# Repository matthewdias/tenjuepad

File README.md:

# tenjuepad
low pro wireless numpad

- choc switches
- designed with nice!nano in mind
- battery headers
- power switch
- art by [pokexe](https://twitter.com/pokexe_art)

## bill of materials

- [Power switch](https://www.mouser.com/ProductDetail/Alps-Alpine/SSAJ120100/?qs=35GPJvxY%252Bl5mRNwFoBrl2g%3D%3D) (optional)
- battery (optional)
- 22 diodes
- nice!nano or other pro micro compatible controller board
- 8 m2 screws
- 4 m2 6mm hex standoffs
- 2 midplates cut from the svg file 3mm thick

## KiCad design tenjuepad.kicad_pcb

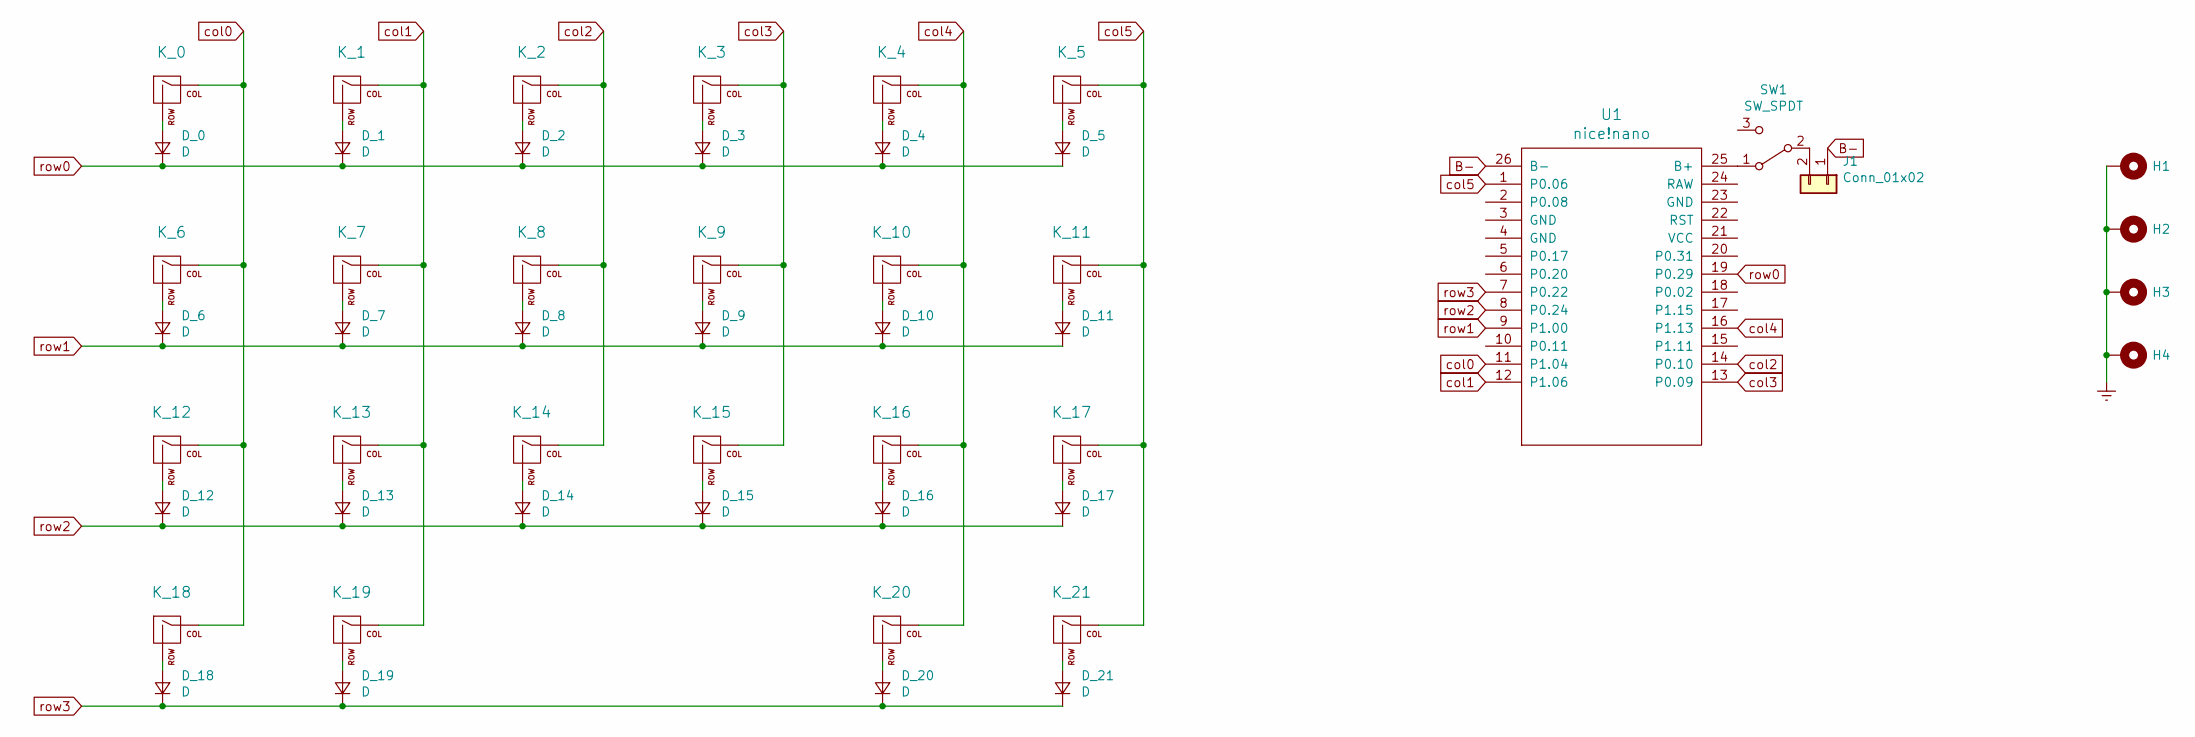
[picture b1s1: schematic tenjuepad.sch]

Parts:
D_0, D_1, D_2, D_3, D_4, D_5, D_6, D_7, D_8, D_9, D_10, D_11, D_12, D_13, D_14, D_15, D_16, D_17, D_18, D_19, D_20, D_21: D; Diode-Hybrid-Back
H1, H2, H3, H4: MountingHole_Pad; MountingHole_2.2mm_M2_Pad_Via
J1: Conn_01x02; PinHeader_1x02_P2.54mm_Vertical
K_0, K_1, K_2, K_3, K_4, K_5, K_6, K_7, K_8, K_9, K_10, K_11, K_12, K_13, K_14, K_15, K_16, K_17, K_18, K_19, K_20, K_21: KEYSW; KailhChoc-1U
SW1: SW_SPDT; SSAJ120100
U1: nice!nano; nicenano

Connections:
B-: J1.1, U1.26 (B-)
Earth: H1.1, H2.1, H3.1, H4.1
unnamed: D_0.2 (A), K_0.2 (ROW)
unnamed: D_1.2 (A), K_1.2 (ROW)
unnamed: D_2.2 (A), K_2.2 (ROW)
unnamed: D_3.2 (A), K_3.2 (ROW)
unnamed: D_4.2 (A), K_4.2 (ROW)
unnamed: D_5.2 (A), K_5.2 (ROW)
unnamed: D_6.2 (A), K_6.2 (ROW)
unnamed: D_7.2 (A), K_7.2 (ROW)
unnamed: D_8.2 (A), K_8.2 (ROW)
unnamed: D_9.2 (A), K_9.2 (ROW)
unnamed: D_10.2 (A), K_10.2 (ROW)
unnamed: D_11.2 (A), K_11.2 (ROW)
unnamed: D_12.2 (A), K_12.2 (ROW)
unnamed: D_13.2 (A), K_13.2 (ROW)
unnamed: D_14.2 (A), K_14.2 (ROW)
unnamed: D_15.2 (A), K_15.2 (ROW)
unnamed: D_16.2 (A), K_16.2 (ROW)
unnamed: D_17.2 (A), K_17.2 (ROW)
unnamed: D_18.2 (A), K_18.2 (ROW)
unnamed: D_19.2 (A), K_19.2 (ROW)
unnamed: D_20.2 (A), K_20.2 (ROW)
unnamed: D_21.2 (A), K_21.2 (ROW)
unnamed: J1.2, SW1.2 (B)
unnamed: SW1.1 (A), U1.25 (B+)
col0: K_0.1 (COL), K_6.1 (COL), K_12.1 (COL), K_18.1 (COL), U1.11 (P1.04)
col1: K_1.1 (COL), K_7.1 (COL), K_13.1 (COL), K_19.1 (COL), U1.12 (P1.06)
col2: K_2.1 (COL), K_8.1 (COL), K_14.1 (COL), U1.14 (P0.10)
col3: K_3.1 (COL), K_9.1 (COL), K_15.1 (COL), U1.13 (P0.09)
col4: K_4.1 (COL), K_10.1 (COL), K_16.1 (COL), K_20.1 (COL), U1.16 (P1.13)
col5: K_5.1 (COL), K_11.1 (COL), K_17.1 (COL), K_21.1 (COL), U1.1 (P0.06)
row0: D_0.1 (K), D_1.1 (K), D_2.1 (K), D_3.1 (K), D_4.1 (K), D_5.1 (K), U1.19 (P0.29)
row1: D_6.1 (K), D_7.1 (K), D_8.1 (K), D_9.1 (K), D_10.1 (K), D_11.1 (K), U1.9 (P1.00)
row2: D_12.1 (K), D_13.1 (K), D_14.1 (K), D_15.1 (K), D_16.1 (K), D_17.1 (K), U1.8 (P0.24)
row3: D_18.1 (K), D_19.1 (K), D_20.1 (K), D_21.1 (K), U1.7 (P0.22)

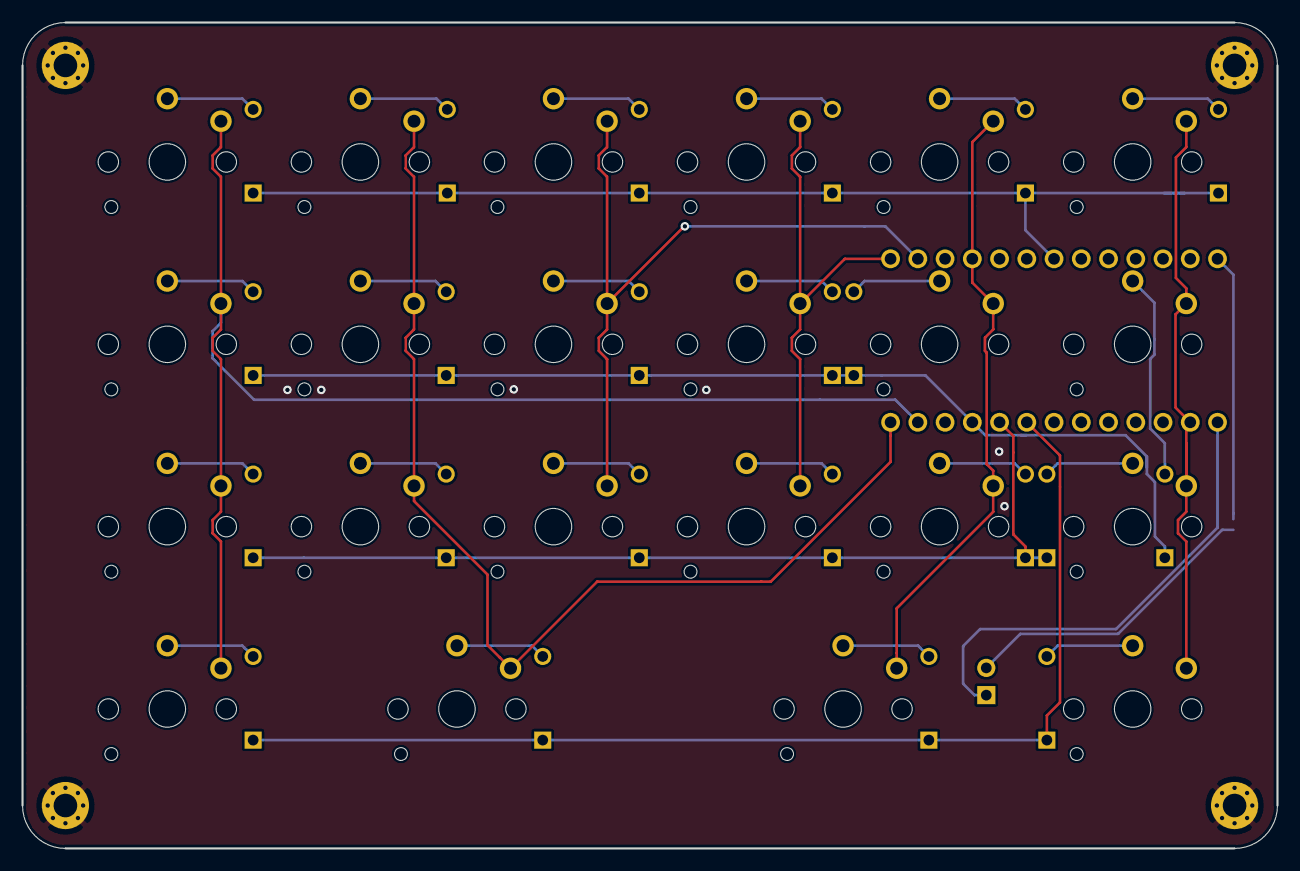
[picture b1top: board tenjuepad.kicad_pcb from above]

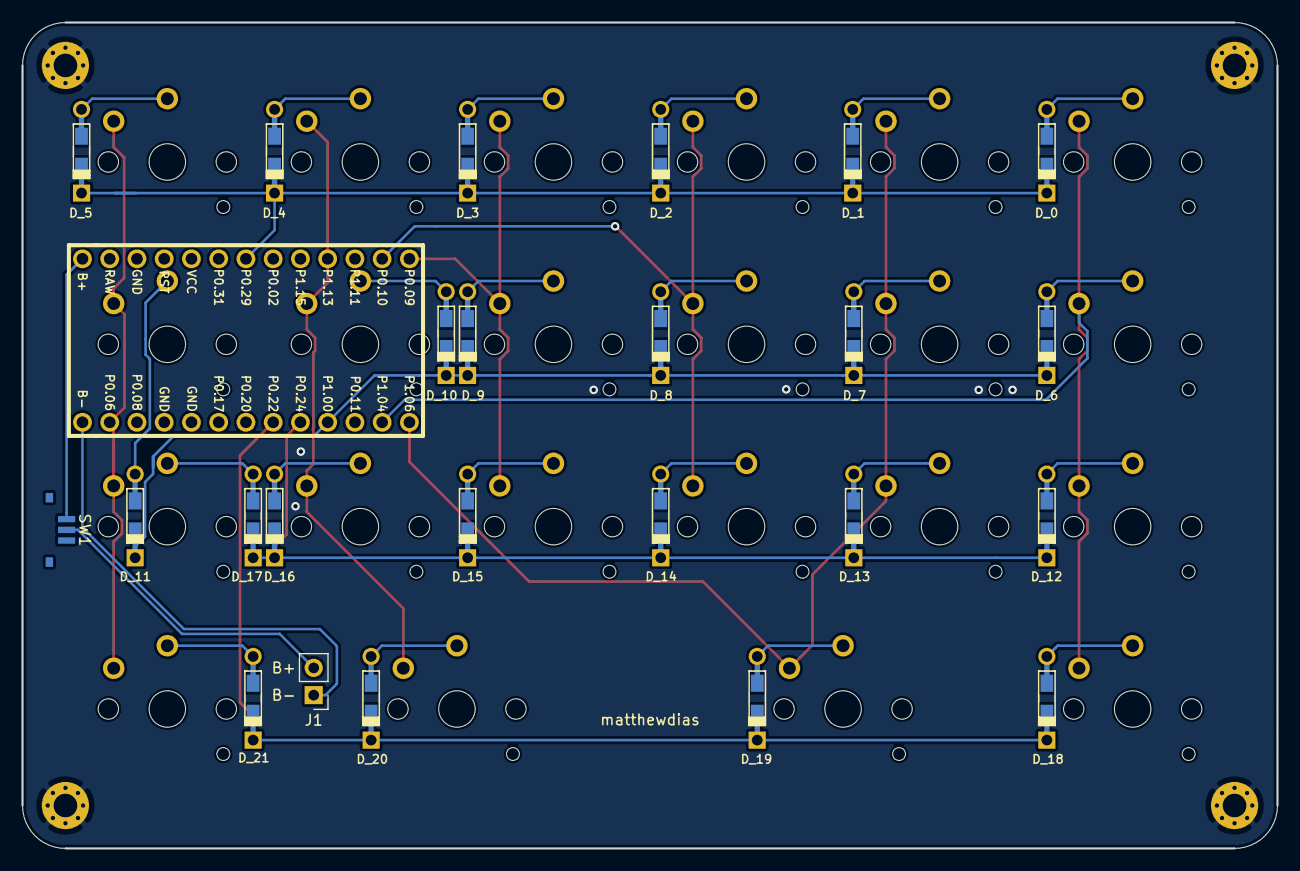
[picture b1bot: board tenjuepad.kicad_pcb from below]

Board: 2 copper layers, 117.0 x 77.0 mm, 51 parts (3 on the bottom side), 36 nets.

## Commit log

2021-01-31 Add readme
2021-01-31 Credit
2021-01-31 Add bom
